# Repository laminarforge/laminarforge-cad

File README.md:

# laminarforge-cad

Parametric CAD models for the LaminarForge open-source diagnostics platform, written in Rust using the [`vcad`](https://crates.io/crates/vcad) crate. Core LAMP/CRISPR device CAD is now built around a sealed disposable diagnostic cartridge rather than loose PCR tubes. Shared constants live in `src/lib.rs`, device and validation generators live in `src/bin/`, and PCB routing lives in `src/pcb/`.

## Local iteration

Use the local `laminarforge_build` MCP tool with an explicit `bin`:

| Change | Action | Purpose |
| --- | --- | --- |
| Rust source validation | `check` | Check one target without code generation. |
| Rust source needs execution | `run`, profile `dev` | Build and run one target. |
| Runtime TOML only, executable already built from the intended source | `execute`, profile `dev` | Generate outputs without invoking Cargo. |
| Final optimized output | `run`, profile `release` | Explicitly optimize the selected target. |

The priming fixture accepts runtime TOML. Other models vary: some already read
configuration, while others use compiled constants. See [the iteration guide](docs/cad-iteration.md)
for exact tool arguments and verification requirements, and [the workflow audit](docs/cad-workflow-audit-2026-09-13.md)
for the remaining improvements.

## Source and delivery

`main` is canonical. Builds and CAD generation run locally on the Mac. AWS,
GitHub Actions and Namespace processing are retired; GitHub stores source only.
Pushing or tagging does not build or publish model outputs. Validate each
changed model and deliver its explicit output files through the local workflow.
PCB manufacturing output must also pass the [routing and release standard](docs/pcba_routing_and_release_standard.md).

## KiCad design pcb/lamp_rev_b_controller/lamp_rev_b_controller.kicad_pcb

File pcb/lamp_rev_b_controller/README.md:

# LAMP Rev B Controller PCBA

Source-package ticket: `T-4C206871`<br>
Manufacturer-handoff ticket: `T-E36FA2C2`<br>
Electrical release evidence: `A-9F7C4851`

This directory is the deterministic source for the Rev B controller carrier. The promoted copper/electrical design is fabrication-clean. Manufacturer-order readiness is a separate fail-closed state owned by `lamp_rev_b_controller_fab_release`.

## Routing and release policy

All routing and manufacturer-release work is governed by the mandatory [LaminarForge PCBA Routing and Release Standard](../../docs/pcba_routing_and_release_standard.md). The board-specific fixture and evidence are:

- [`freerouting_benchmark.toml`](freerouting_benchmark.toml): pinned router/tool settings and the 1,200-second runtime cap;
- [`freerouting_benchmark.md`](freerouting_benchmark.md): harness operation and determinism limitations;
- [`benchmarks/freerouting_v2_1_0_pass_sweep.md`](benchmarks/freerouting_v2_1_0_pass_sweep.md) and its [JSON record](benchmarks/freerouting_v2_1_0_pass_sweep.json): exact 1→10→50 matrix evidence;
- [`benchmarks/freerouting_v2_1_0_promotion.md`](benchmarks/freerouting_v2_1_0_promotion.md): first-clean promotion-attempt evidence; and
- [`electrical_release_evidence.md`](electrical_release_evidence.md), [`fab_release.toml`](fab_release.toml), and [`release_manifest.toml`](release_manifest.toml): electrical, fabrication, and deterministic-package gates.

These files specialize the general policy for Rev B; they do not replace it. Routing and SES validation remain scratch-only until every promotion gate passes.

## Locked first-article population

- Variant: `rev_b_12v_first_article`; 5 assembled top-side PCBAs.
- `R25` and `R26`: mandatory DNP. Populating either bypasses its heater MOSFET and can energize the heater whenever `VIN_HEATER` is present.
- `R55`: populate only for this 12 V variant; DNP for 24 V unless an approved regulated 12 V VDRV path is present.
- `J24`: connect through an external normally-closed thermal cutoff or a correctly rated jumper before heater tests. Do not bridge `VIN_PROTECTED` to `VIN_HEATER` in copper.
- `LDD-1000H` and `P7812-500R` alternates: DNP for this release.
- Panelization: fabricator-owned from the released single-up board; portal preview approval is mandatory.

## Authoritative workflow

Run the repository contract and release command through the LaminarForge build tool:

```json
{"repo":"laminarforge-cad","action":"run","bin":"lamp_rev_b_controller_check"}
```

```json
{"repo":"laminarforge-cad","action":"run","bin":"lamp_rev_b_controller_fab_release"}
```

The release command requires a clean full commit equal to `origin/main` and KiCad `10.0.3`. It writes every KiCad report/export to two ignored temporary trees, normalizes known time metadata, compares every staged byte, and promotes only identical results.

When every external choice is controlled, it emits:

- nine fabrication Gerbers plus the Gerber job file;
- separate F/B paste Gerbers;
- separate PTH/NPTH Excellon drills, both drill maps, and drill report;
- fabrication and top/bottom assembly PDFs;
- formal BOM, CPL, DNP, and no-substitution CSVs;
- schematic PDF, top/bottom renders, board-only mechanical STEP, source snapshot, notes, and electrical evidence;
- `MANIFEST.json`, `SHA256SUMS`, upload units, and a normalized outer handoff ZIP.

If procurement, stackup/order fields, or portal approval remain unresolved, it still preserves the byte-reproducible review tree and exact blocker report, exits nonzero, and emits neither `upload/` nor the outer handoff ZIP.

## Current external blockers

Repository evidence does not define a selected manufacturer/order profile, physical dielectric stackup, fabrication tolerances/class, final finish specification, colors, or an impedance-policy decision. `parts.toml` also lacks explicit manufacturer/MPN fields and contains unresolved supplier prose/manual selections. No portal preview has been approved. These are manufacturing choices, not electrical design defects; do not invent them and do not treat the provisional artifact `A-D87AC12B` as vendor-cited research.

Any source, population, placement, schematic, stackup, or copper change invalidates prior evidence and requires fresh DRC/connectivity/ERC/BOM/CPL/reproducibility gates.

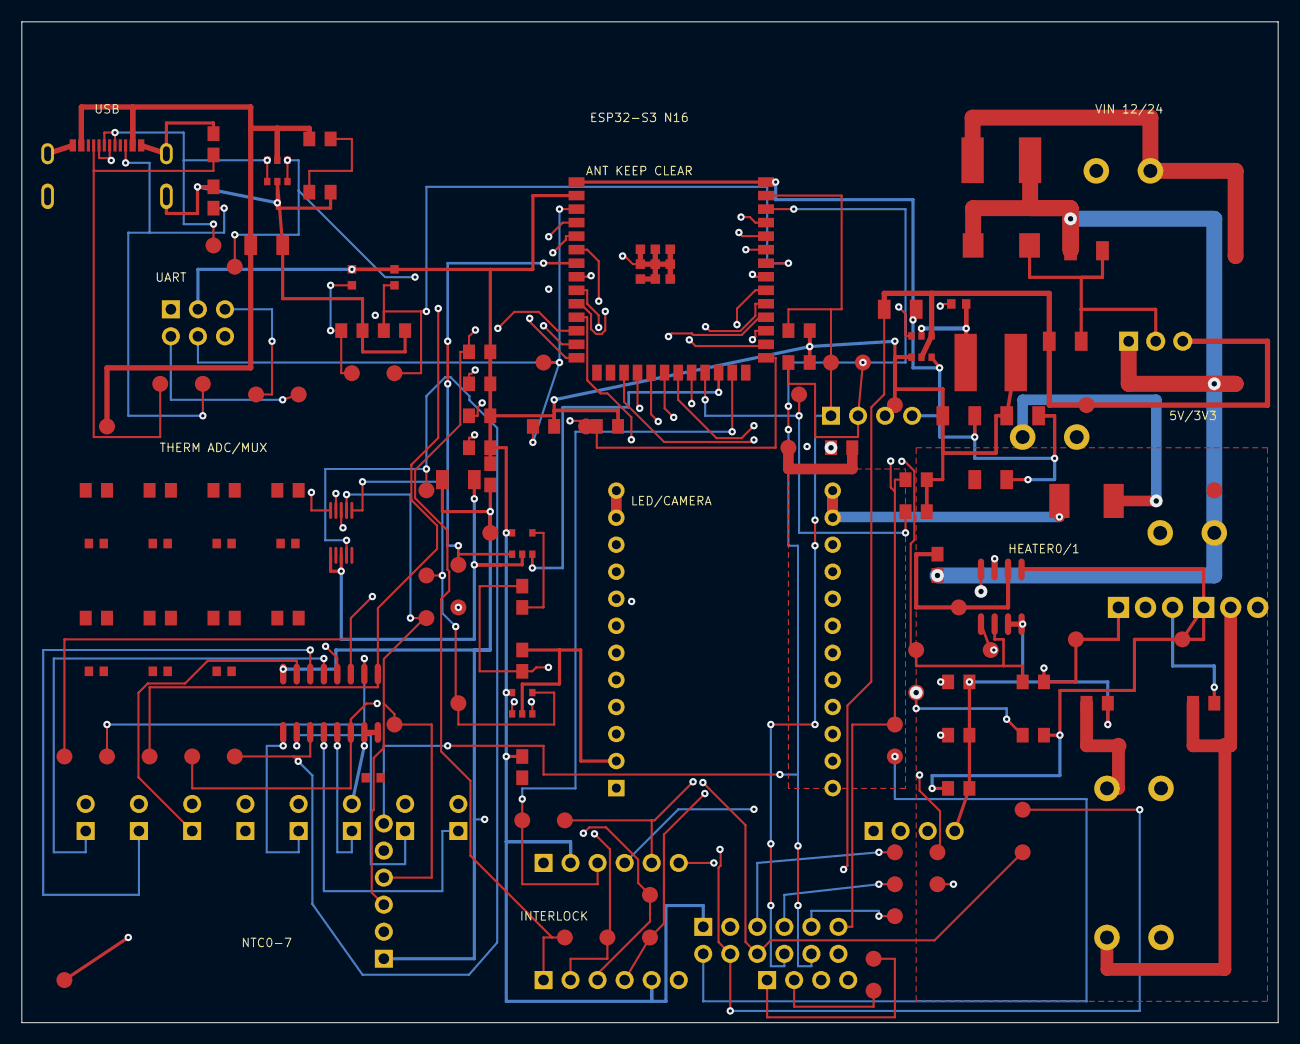
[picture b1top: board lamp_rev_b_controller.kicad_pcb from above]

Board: 4 copper layers, 118.0 x 94.0 mm, 153 parts (0 on the bottom side), 72 nets.

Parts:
C1, C5, C6: 22uF rail bulk; C1206
C2: 22uF >=10V +5V buck output; C1206
C3: 22uF AP63203 input; C1206
C4: 22uF 50V VIN buck input; C1206
C7, C8: 22uF AP63203 output; C1206
C9: 100nF bootstrap; C0603
C10, C11, C12, C13, C14, C15, C16, C17: 100nF; C0603
D1: SMBJ18A footprint option; SMB_L4.6-W3.6-LS5.3-RD
D2, D3: LED0603 status; LED0603-RD
F1: RUEF500K/PTC; FUSE2920
FB1: 0805 ferrite bead / approved analog rail link fro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; R0805
J1: TYPE-C 3.1 MT 16P; USB-C-SMD_TYPE-C-USB-4
J2, J12, J13, J15: DB128H-5.08-2P-BK-S; TERM-BLOCK-5.08-2P
J4, J5, J6, J7, J8, J9, J10, J11: 2-pin NTC header; PINHEADER_1X02_2.54MM
J16: LED NTC/ID header; PINHEADER_1X04_2.54MM
J17: External camera sync header; PINHEADER_1X06_2.54MM
J18: SPI/FIFO camera module header; PINHEADER_2X06_2.54MM
J19: Lid/cartridge/cutoff interlock header; PINHEADER_1X06_2.54MM
J20: Fan PWM/tach header; PINHEADER_1X04_2.54MM
J21: 2x3 UART/programming header; PINHEADER_2X03_2.54MM
J22: I2C expansion header; PINHEADER_1X04_2.54MM
J23: Analog optical diagnostic header; PINHEADER_1X06_2.54MM
J24: DB128H-5.08-2P high-current heater cutoff loop/li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; TERM-BLOCK-5.08-2P
L1: Wurth 74439346068 6.8uH shielded inductor; IND_74439346068
Q1, Q2: IRLB3813PBF TO-220 12V prototype; TO-220-3_VERTICAL
R1, R2: 5.1k; R0805
R3, R4: 100k/100k VBUS sense; R0805
R10, R11, R12, R13, R14, R15, R16, R17: 10k 0.1%; R0805
R20, R21: 33R; R0805
R22, R23, R24, R48, R49: 10k; R0805
R25, R26: 50mR DNP option; R0805
R30, R31: 1k; R0805
R40, R41, R42, R43, R44, R45, R46, R47: 4.7k; R0805
R50: 100R LED DIM series; R0805
R51: 100k LED DIM pulldown; R0805
R52: 0R LED_SUPPLY feed link from VIN_PROTECTED; R0805
R53: 0.1R 1% >=1W LED current shunt; R2512
R54: 10k LED_FAULT_N pull-up; R0805
R55: 0R VDRV feed link from VIN_PROTECTED, 12 V popula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; R0805
TP_3V3: +3V3; TESTPOINT_SMD_1.5MM
TP_3V3A: +3V3_ANA; TESTPOINT_SMD_1.5MM
TP_5V: +5V; TESTPOINT_SMD_1.5MM
TP_ADS_AIN0: THERM_MUX_OUT; TESTPOINT_SMD_1.5MM
TP_ADS_AIN2: LED_CURRENT_SENSE; TESTPOINT_SMD_1.5MM
TP_ADS_AIN3: AUX_ANALOG_IN; TESTPOINT_SMD_1.5MM
TP_AUX_ANALOG: AUX_ANALOG_IN; TESTPOINT_SMD_1.5MM
TP_BOOT: ESP_GPIO0_BOOT; TESTPOINT_SMD_1.5MM
TP_CAM_CS: CAM_CS_N; TESTPOINT_SMD_1.5MM
TP_CAM_FRAME: CAM_FRAME_INT; TESTPOINT_SMD_1.5MM
TP_CAM_PWDN: CAM_PWDN_N; TESTPOINT_SMD_1.5MM
TP_CAM_RESET: CAM_RESET_N; TESTPOINT_SMD_1.5MM
TP_CART: CART_PRESENT_N; TESTPOINT_SMD_1.5MM
TP_CUTOFF: AUX_IO0_THERMAL_CUTOFF_OK; TESTPOINT_SMD_1.5MM
TP_EN: ESP_EN; TESTPOINT_SMD_1.5MM
TP_EXPOSURE: EXPOSURE_ACTIVE_IN; TESTPOINT_SMD_1.5MM
TP_FAN_PWM: FAN_PWM; TESTPOINT_SMD_1.5MM
TP_FAN_TACH: FAN_TACH; TESTPOINT_SMD_1.5MM
TP_FAULT: STATUS_FAULT_LED; TESTPOINT_SMD_1.5MM
TP_FRAME_TRIG: FRAME_TRIG_OUT; TESTPOINT_SMD_1.5MM
TP_GND: GND; TESTPOINT_SMD_1.5MM
TP_HEATER0_GATE: HEATER0_GATE; TESTPOINT_SMD_1.5MM
TP_HEATER0_LOW: HEATER0_LOW; TESTPOINT_SMD_1.5MM
TP_HEATER0_PWM: HEATER0_PWM; TESTPOINT_SMD_1.5MM
TP_HEATER1_GATE: HEATER1_GATE; TESTPOINT_SMD_1.5MM
TP_HEATER1_LOW: HEATER1_LOW; TESTPOINT_SMD_1.5MM
TP_HEATER1_PWM: HEATER1_PWM; TESTPOINT_SMD_1.5MM
TP_HEATER_ARM: HEATER_ARM; TESTPOINT_SMD_1.5MM
TP_I2C_SCL: I2C_SCL; TESTPOINT_SMD_1.5MM
TP_I2C_SDA: I2C_SDA; TESTPOINT_SMD_1.5MM
TP_LATCH: LATCH_LOCKED_N; TESTPOINT_SMD_1.5MM
TP_LED_EN: LED_EXC_EN; TESTPOINT_SMD_1.5MM
TP_LED_PWM: LED_EXC_PWM; TESTPOINT_SMD_1.5MM
TP_LED_SENSE: LED_CURRENT_SENSE; TESTPOINT_SMD_1.5MM
TP_LED_SUPPLY: LED_SUPPLY; TESTPOINT_SMD_1.5MM
TP_LED_SYNC: LED_SYNC_OUT; TESTPOINT_SMD_1.5MM
TP_LID: LID_CLOSED_N; TESTPOINT_SMD_1.5MM
TP_RUN: STATUS_RUN_LED; TESTPOINT_SMD_1.5MM
TP_SD_CS: SD_CS_N; TESTPOINT_SMD_1.5MM
TP_SPARE42: SPARE_GPIO42; TESTPOINT_SMD_1.5MM
TP_SPI_MISO: SPI_MISO; TESTPOINT_SMD_1.5MM
TP_SPI_MOSI: SPI_MOSI; TESTPOINT_SMD_1.5MM
TP_SPI_SCLK: SPI_SCLK; TESTPOINT_SMD_1.5MM
TP_THERM_EN: THERM_MUX_EN_N; TESTPOINT_SMD_1.5MM
TP_THERM_OUT: THERM_MUX_OUT; TESTPOINT_SMD_1.5MM
TP_THERM_S0: THERM_MUX_S0; TESTPOINT_SMD_1.5MM
TP_THERM_S1: THERM_MUX_S1; TESTPOINT_SMD_1.5MM
TP_THERM_S2: THERM_MUX_S2; TESTPOINT_SMD_1.5MM
TP_UART_RX: UART0_RXD; TESTPOINT_SMD_1.5MM
TP_UART_TX: UART0_TXD; TESTPOINT_SMD_1.5MM
TP_USB_CC1: USB_CC1; TESTPOINT_SMD_1.5MM
TP_USB_CC2: USB_CC2; TESTPOINT_SMD_1.5MM
TP_USB_DN: USB_DN; TESTPOINT_SMD_1.5MM
TP_USB_DP: USB_DP; TESTPOINT_SMD_1.5MM
TP_VBUS: VBUS; TESTPOINT_SMD_1.5MM
TP_VDRV: VDRV; TESTPOINT_SMD_1.5MM
TP_VIN: VIN_12_24; TESTPOINT_SMD_1.5MM
TP_VIN_HEATER: VIN_HEATER; TESTPOINT_SMD_1.5MM
TP_VIN_PROT: VIN_PROTECTED; TESTPOINT_SMD_1.5MM
U1: ESP32-S3-WROOM-1-N16; WIFIM-SMD_ESP32-S3-WROOM-1-N8
U2: USBLC6-2SC6; SOT-23-6
U3: Diodes AP63203WU-7 fixed 3.3V 2A buck; TSOT26_AP63203WU
U4: ADS1115IDGSR; MSOP-10_L3.0-W3.0-P0.50-LS5.0-BL
U5: CD74HC4051M; SOIC-16_L9.9-W3.9-P1.27-LS6.0-BL
U6: TC4427ACOA/TC4427EPA; SOIC-8_L4.9-W3.9-P1.27-LS6.0-BL
U7: CUI/Bel P7805-2000-S 5V 2A 8-36V buck module; han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; P78-2000-S_SIP3
U8: Mean Well LDD-700H 700mA CC buck LED driver; LDD-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; MEANWELL_LDD-300-1000H_THT
U9: SN74LVC1G08DBVR LED_EXC_PWM AND LED_EXC_EN; SOT-23-5
U10: INA180A1IDBVR gain 20 LED current sense; SOT-23-5

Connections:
3V3_BST: C9.1, U3.6
3V3_SW: C9.2, L1.1, U3.5
+3V3: C7.1, C8.1, D2.2, D3.2, FB1.1, J17.2, J18.1, J19.5, J21.2, J22.3, L1.2, R40.2, R41.2, R42.2, R43.2, R44.2, R45.2, R46.2, R47.2, R48.2, R49.2, R54.2, TP_3V3.1, U1.2, U3.1, U4.8, U9.5, U10.5
+3V3_ANA: C5.1, FB1.2, J16.3, J23.1, TP_3V3A.1, U5.16
+5V: C2.1, C3.1, J20.3, TP_5V.1, U3.2, U3.4, U7.3
AUX_ANALOG_IN: J16.2, J23.3, J23.4, TP_ADS_AIN3.1, TP_AUX_ANALOG.1, U4.7
AUX_IO0_THERMAL_CUTOFF_OK: J19.4, R47.1, TP_CUTOFF.1, U1.32
CAM_CS_N: J18.6, R42.1, TP_CAM_CS.1, U1.20
CAM_FRAME_INT: J18.7, TP_CAM_FRAME.1, U1.21
CAM_PWDN_N: J18.9, TP_CAM_PWDN.1, U1.22
CAM_RESET_N: J18.8, TP_CAM_RESET.1, U1.8
CART_PRESENT_N: J19.2, R45.1, TP_CART.1, U1.31
ESP_EN: J21.5, R48.1, TP_EN.1, U1.3
ESP_GPIO0_BOOT: J21.6, R49.1, TP_BOOT.1, U1.27
EXPOSURE_ACTIVE_IN: J17.4, TP_EXPOSURE.1, U1.29
FAN_PWM: J20.1, TP_FAN_PWM.1
FAN_TACH: J20.2, TP_FAN_TACH.1
FRAME_TRIG_OUT: J17.3, TP_FRAME_TRIG.1, U1.25
GND: C1.2, C2.2, C3.2, C4.2, C5.2, C6.2, C7.2, C8.2, D1.2, J1.13, J1.14, J1.15, J1.16, J1.A12B1, J1.B12A1, J2.2, J4.2, J5.2, J6.2, J7.2, J8.2, J9.2, J10.2, J11.2, J16.4, J17.1, J18.2, J18.12, J19.6, J20.4, J21.1, J22.4, J23.2, Q1.3, Q2.3, R1.2, R2.2, R4.2, R22.2, R23.2, R24.2, R25.2, R26.2, R30.2, R31.2, R51.2, TP_GND.1, U1.1, U1.40, U1.41, U2.2, U3.3, U4.1, U4.3, U5.7, U5.8, U6.3, U6.4, U7.2, U8.1, U8.2, U9.2, U10.2
HEATER0_GATE: Q1.1, R20.2, R23.1, TP_HEATER0_GATE.1, U6.7
HEATER0_LOW: J12.2, Q1.2, R25.1, TP_HEATER0_LOW.1
HEATER0_PWM: R20.1, TP_HEATER0_PWM.1, U1.10, U6.2
HEATER1_GATE: Q2.1, R21.2, R24.1, TP_HEATER1_GATE.1, U6.5
HEATER1_LOW: J13.2, Q2.2, R26.1, TP_HEATER1_LOW.1
HEATER1_PWM: R21.1, TP_HEATER1_PWM.1, U1.11, U6.8
HEATER_ARM: R22.1, TP_HEATER_ARM.1, U1.9, U6.1
I2C_SCL: J18.11, J22.2, J23.6, R41.1, TP_I2C_SCL.1, U1.38, U4.10
I2C_SDA: J18.10, J22.1, J23.5, R40.1, TP_I2C_SDA.1, U1.39, U4.9
LATCH_LOCKED_N: J19.3, R46.1, TP_LATCH.1
LED_CURRENT_SENSE: TP_ADS_AIN2.1, TP_LED_SENSE.1, U4.6, U10.4
LED_DIM_DRIVE: R50.2, R51.1, U8.22
LED_DIM_GATE: R50.1, U9.4
LED_DRV_PLUS: R53.1, U8.13, U8.14, U10.1
LED_EXC_EN: TP_LED_EN.1, U1.24, U9.3
LED_EXC_PWM: TP_LED_PWM.1, U1.7, U9.1
LED_MINUS: J15.2, U8.11, U8.12
LED_PLUS: J15.1, R53.2, U10.3
LED_SUPPLY: R52.2, TP_LED_SUPPLY.1, U8.23, U8.24
LED_SYNC_OUT: J17.5, TP_LED_SYNC.1, U1.28
LID_CLOSED_N: J19.1, R44.1, TP_LID.1, U1.30
SD_CS_N: R43.1, TP_SD_CS.1, U1.23
SPARE_GPIO42: J17.6, TP_SPARE42.1, U1.35
SPI_MISO: J18.5, TP_SPI_MISO.1, U1.19
SPI_MOSI: J18.4, TP_SPI_MOSI.1, U1.18
SPI_SCLK: J18.3, TP_SPI_SCLK.1, U1.17
STATUS_FAULT_LED: D3.1, R31.1, TP_FAULT.1, U1.34
STATUS_RUN_LED: D2.1, R30.1, TP_RUN.1, U1.33
THERM_CH_0: J4.1, U5.13
THERM_CH_1: J5.1, U5.14
THERM_CH_2: J6.1, U5.15
THERM_CH_3: J7.1, U5.12
THERM_CH_4: J8.1, U5.1
THERM_CH_5: J9.1, J16.1, U5.5
THERM_CH_6: J10.1, U5.2
THERM_CH_7: J11.1, U5.4
THERM_MUX_EN_N: TP_THERM_EN.1, U1.12, U5.6
THERM_MUX_OUT: TP_ADS_AIN0.1, TP_THERM_OUT.1, U4.4, U5.3
THERM_MUX_S0: TP_THERM_S0.1, U1.4, U5.11
THERM_MUX_S1: TP_THERM_S1.1, U1.5, U5.10
THERM_MUX_S2: TP_THERM_S2.1, U1.6, U5.9
UART0_RXD: J21.4, TP_UART_RX.1, U1.36
UART0_TXD: J21.3, TP_UART_TX.1, U1.37
USB_CC1: J1.A5, R1.1, TP_USB_CC1.1
USB_CC2: J1.B5, R2.1, TP_USB_CC2.1
USB_DN: J1.A7, J1.B7, TP_USB_DN.1, U1.13, U2.3, U2.4
USB_DP: J1.A6, J1.B6, TP_USB_DP.1, U1.14, U2.1, U2.6
USB_VBUS_SENSE: R3.2, R4.1
VBUS: C1.1, J1.A9B4, J1.B9A4, R3.1, TP_VBUS.1, U2.5
VDRV: R55.2, TP_VDRV.1, U6.6
VIN_12_24: F1.1, J2.1, TP_VIN.1
VIN_HEATER: C6.1, J12.1, J13.1, J24.2, TP_VIN_HEATER.1
VIN_PROTECTED: C4.1, D1.1, F1.2, J24.1, R52.1, R55.1, TP_VIN_PROT.1, U7.1

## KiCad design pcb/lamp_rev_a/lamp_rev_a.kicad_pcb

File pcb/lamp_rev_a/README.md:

# LaminarForge LAMP Rev A PCBA

This directory is the source package for the real one-board LAMP PCBA.

The goal is one 4-layer ESP32-S3 board that can be checked, laid out in KiCad,
exported for JLCPCB, and iterated without going back to the old generated-layout
workflow.

## Source Of Truth

- `contract.toml`: board requirements, rails, nets, GPIO map, test points, and verification gates.
- `parts.toml`: selected schematic parts plus explicit fab-blocking part-selection gaps.
- `power_architecture.toml`: locked Rev A power topology and the explicit no-buck decision.
- `optical_architecture.toml`: locked Rev A optical topology, wavelength, detector, and front-end decision.
- `optical_mode.md`: human-readable optical-mode decision and bench validation gate.
- `placement.toml`: locked starting refs, coordinates, test points, and eight-slot optical geometry.
- `pin_nets.toml`: conservative footprint pad-to-net assignments for known package pinouts.
- `firmware_handoff.toml`: ESP32-S3 module-pin to SoC-GPIO handoff, slot map, and firmware bring-up notes.
- `electrical_validation.toml`: pre-fab electrical validation assumptions, derating gates, current-path checks, and simulation handoff sources.
- `routing_plan.toml`: routing phase order, current unrouted count, autorouter policy, and release gates.
- `routing_seed.toml`: DRC-clean starter traces emitted into the materialized board.
- `copper_zones.toml`: controlled KiCad copper pours, starting with front/back GND zones.
- `fab_release.toml`: repeatable KiCad CLI export contract for Gerbers, drill files, assembly files, STEP, and release reports.
- `lamp_rev_a.kicad_sch`: KiCad schematic shell for the one-board Rev A electrical architecture.
- `lamp_rev_a.kicad_pcb`: materialized KiCad board with the Rev A outline, 4-layer stack, placed footprints, test points, and optical-slot guides.
- `lamp_rev_a.kicad_pro`: KiCad project shell.
- `sym-lib-table` / `fp-lib-table`: project-local library tables pointing at the locked `pcb/lib/lcsc` symbols and footprints.
- `lamp_rev_a.kicad_dru`: custom KiCad design rules for power, heater, analog, and USB constraints.
- `kibot.yaml`: intended fab/report export pipeline once the schematic and placed board exist.

Rust should validate contracts and automate exports. KiCad should own the
schematic and PCB layout.

## Iteration Flow

```text
contract.toml + parts.toml
  -> cargo run --release --bin lamp_pcba_check
  -> placement.toml refs and zone checks
  -> pin_nets.toml trusted pad assignments
  -> firmware_handoff.toml firmware pin/slot handoff checks
  -> electrical_validation.toml power, derating, heater, GPIO, USB, and simulation checks
  -> cargo run --release --bin lamp_rev_a_materialize_board
  -> cargo run --release --bin lamp_rev_a_seed_routes_from_drc when reseeding short safe traces
  -> cargo run --release --bin lamp_rev_a_route_greedy for DRC-gated route iteration
  -> kicad-cli pcb drc --refill-zones for zone-connected routing checks
  -> KiCad schematic capture in lamp_rev_a.kicad_sch
  -> KiCad ERC
  -> footprint/BOM/JLC field lock
  -> KiCad placement cleanup from the materialized board
  -> KiCad interactive routing
  -> KiCad DRC + schematic/PCB parity
  -> KiBot/KiKit fab outputs
  -> physical bring-up measurements
  -> update contract.toml for the next revision
```

## Board Decisions

- One physical board for Rev A.
- 4-layer stack: `F.Cu`, `In1.Cu` ground plane, `In2.Cu` power plane, `B.Cu`.
- ESP32-S3 module, not a bare ESP32 chip.
- USB VBUS is the Rev A electronics 5 V source through a Schottky path; +3V3 is derived locally.
- The 12 V input is reserved for heater power. Do not add a 12 V to 5 V buck unless standalone non-USB operation becomes a new explicit Rev change.
- External heater element driven from the board through a protected high-current output.
- Heater path protection is locked as board-side resettable fuse + TVS + 5.08 mm heater terminal, with an external inline KSD9700 thermal cutoff mounted on the heater assembly.
- Optical mode is locked to 650 nm red-light turbidimetry with eight LED/photodiode channels, muxed into one TIA and ADC path.
- Starting placement is locked in `placement.toml`: 91 top-side footprints, 16 test points, and 8 optical slots at 12 mm pitch.
- Test points are mandatory for rails, heater control/output, I2C, UART, boot/reset, ADC, and mux output.

## Local Checks

Run:

```bash
cargo run --release --bin lamp_pcba_check
cargo run --release --bin lamp_rev_a_electrical_validate
cargo run --release --bin lamp_rev_a_spice_check
cargo run --release --bin lamp_rev_a_materialize_board
cargo run --release --bin lamp_rev_a_fab_preview
cargo run --release --bin lamp_rev_a_fab_release
cargo run --release --bin lamp_rev_a_route_report
cargo build --release --bin lamp_rev_a_materialize_board --bin lamp_rev_a_route_greedy
LAMP_ROUTE_MAX_ACCEPTS=10 LAMP_ROUTE_MAX_TRIALS=160 target/release/lamp_rev_a_route_greedy
```

`lamp_rev_a_spice_check` requires `ngspice`. `main` CI installs it, runs the
operating-point check against the generated power-path netlist, then runs
`lamp_rev_a_fab_release` on a KiCad-enabled macOS runner and uploads
`lamp-rev-a-pcba-fab-release-<commit>` containing the validated fab release
directory and upload bundles.

The current schematic is an architecture shell, not a fabrication-ready circuit.
The checker should not report fab-blocking part-selection gaps. The board now
materializes all selected parts into KiCad with zero physical DRC violations
with a DRC-clean starter route seed and GND copper pours. The route seed is
currently at 112 accepted segments, zero real unrouted ratlines after KiCad zone
refill, and one ignored KiCad self-zone report item for the front GND pour. The
active work is schematic completion, schematic/PCB parity, fab export validation,
and bench validation.
`lamp_rev_a_fab_release` emits JLCPCB machine-assembly BOM/CPL files separately
from through-hole/manual-install parts, then verifies that required Gerbers,
drills, reports, position files, review STEP output, and the order audit report
are present and non-empty. It also emits validated upload bundles under
`fab_release/bundles/`: fabrication Gerbers/drills, assembly CSVs, and review
artifacts. The release also includes a source snapshot bundle with the exact
KiCad and TOML inputs used to generate the fab package. The review package
includes a bring-up checklist generated from the configured Rev A test points
and a firmware handoff generated from the checked ESP32-S3 pin map. It also
emits an electrical-validation report, a first-order SPICE power-path handoff,
a machine-checked full-speed USB DP/DN routing sanity gate, a
simulation/analysis handoff, generated PDN current-path and thermal power CSVs,
a structured first-article measurement CSV for current-limited rail bring-up,
component derating/stress CSVs for the high-risk electrical parts,
an EMC/ESD pre-compliance CSV for USB, heater, 12 V, Wi-Fi, and analog noise risks,
a USB-C power-budget CSV for Rd/default-current, VBUS/+5V/+3V3 current, inrush linkage, and first-article rail coverage,
a procurement-readiness CSV for critical part ordering, machine/manual assembly, and external safety-component evidence,
a procurement-substitution CSV locking safety-critical LCSC order codes and requiring engineering review for swaps,
a schematic source/parity CSV tying the architecture-shell KiCad schematic to contract modules, selected parts, and required nets,
a connector/polarity CSV for USB-C, manual connectors, diodes, MOSFETs, and orientation-sensitive IC pinouts,
an assembly-orientation CSV for machine-placed ICs, polarity-sensitive parts, CPL centroids, and pin-1 evidence,
an assembly-inspection CSV requiring AOI/photo evidence, linked validation gates, and stop/rework actions for critical parts,
an assembly-fixture/readability CSV requiring visible silkscreen labels, fixture references, photo evidence, and rework actions for critical connectors/test points,
a machine-checked assembly-parity CSV for BOM/CPL/manual/position reference consistency,
a fabrication-capability CSV for board-house stackup, geometry, drill, via, and routing process limits,
an I2C/ADS1115 bus validation CSV for pull-up, rise-time, device identity, and stuck-low coverage,
a heater-protection coordination CSV for PTC, terminal, MOSFET, TVS, external cutoff, and current-limit coverage,
an external-harness safety CSV for 12 V adapter, heater leads, inline cutoff, wire gauge, polarity, and strain relief,
a mechanical-access CSV for service connector, heater terminal, MOSFET, boot/reset, analog, and I2C probe reachability,
an ESP32-S3 startup-safety CSV for boot straps, reset, and heater fail-closed defaults,
a manufacturing-test coverage CSV for critical test points, firmware diagnostics, and release traceability,
a calibration-readiness CSV for heater, ADC, optical, sensor-bus, negative-control, and firmware identity records,
a validation-traceability CSV tying each gate to artifacts, manifest evidence, CI steps, and pass criteria,
a simulation-input CSV for PDN, electrothermal, USB/SI, and EMC handoff readiness,
the first routed-geometry DC PDN simulation CSV for voltage drop and I2R loss,
a lumped thermal-margin simulation CSV for component and routed-copper steady-state estimates,
a heater/reaction-block thermal transient CSV for warm-up, hold, duty, overshoot, and energy estimates,
an ngspice ESP32-S3 reset/boot-strap timing netlist/CSV for EN, GPIO0, and boot-sensitive output startup checks,
an ngspice USB/VBUS hot-plug and 3.3 V startup/inrush netlist/CSV for rail startup envelope checks,
an ngspice 3.3 V rail load-step transient netlist/CSV for ESP32 burst-load sag,
an ngspice power-domain fault/backfeed netlist/CSV for 12 V heater-domain isolation assumptions,
an ngspice optical analog front-end transient netlist/CSV for TIA/ADC signal-envelope range,
an optical crosstalk/mux-settling CSV for slot isolation and ADC sampling assumptions,
an optical signal/noise margin CSV for threshold and negative-control drift assumptions,
and a thermistor/ADC transfer CSV for heater temperature-sense range, sensitivity, and fault coverage,
and a checksum manifest for the fabrication, assembly, and source bundles.
It also mirrors the board STEP review model to `output/lamp_rev_a_board.stp`;
run the CAD conversion for `lamp_rev_a_board` to create
`output/lamp_rev_a_board.usdz` for the Agentic FlowState CAD tab.

Current KiCad checks:

```bash
kicad-cli sch erc pcb/lamp_rev_a/lamp_rev_a.kicad_sch \
  -o pcb/lamp_rev_a/reports/erc.json --format json

kicad-cli pcb drc --refill-zones --format json \
  --output pcb/lamp_rev_a/reports/drc.json \
  pcb/lamp_rev_a/lamp_rev_a.kicad_pcb
```

Expected DRC state at this stage: `0 violations` and no real unrouted
connections. KiCad may still report one self-referential front-GND-zone
`unconnected_items` entry; `lamp_rev_a_route_report` ignores only that exact
self-zone artifact and still reports real ratlines by net.

`lamp_rev_a_seed_routes_from_drc` is intentionally conservative: it only seeds
short direct routes that preserve zero physical DRC violations. Longer routes
must be added deliberately in `routing_seed.toml`, accepted by
`lamp_rev_a_route_greedy`, or finished in KiCad. `lamp_rev_a_route_greedy`
mechanically tries candidate routes, runs KiCad DRC, and keeps only candidates
that reduce `unconnected_items` while preserving zero physical DRC violations.

Do not accept autorouter output by itself. Use it to expose bad placement or
constraint problems, then finish and review the layout in KiCad.

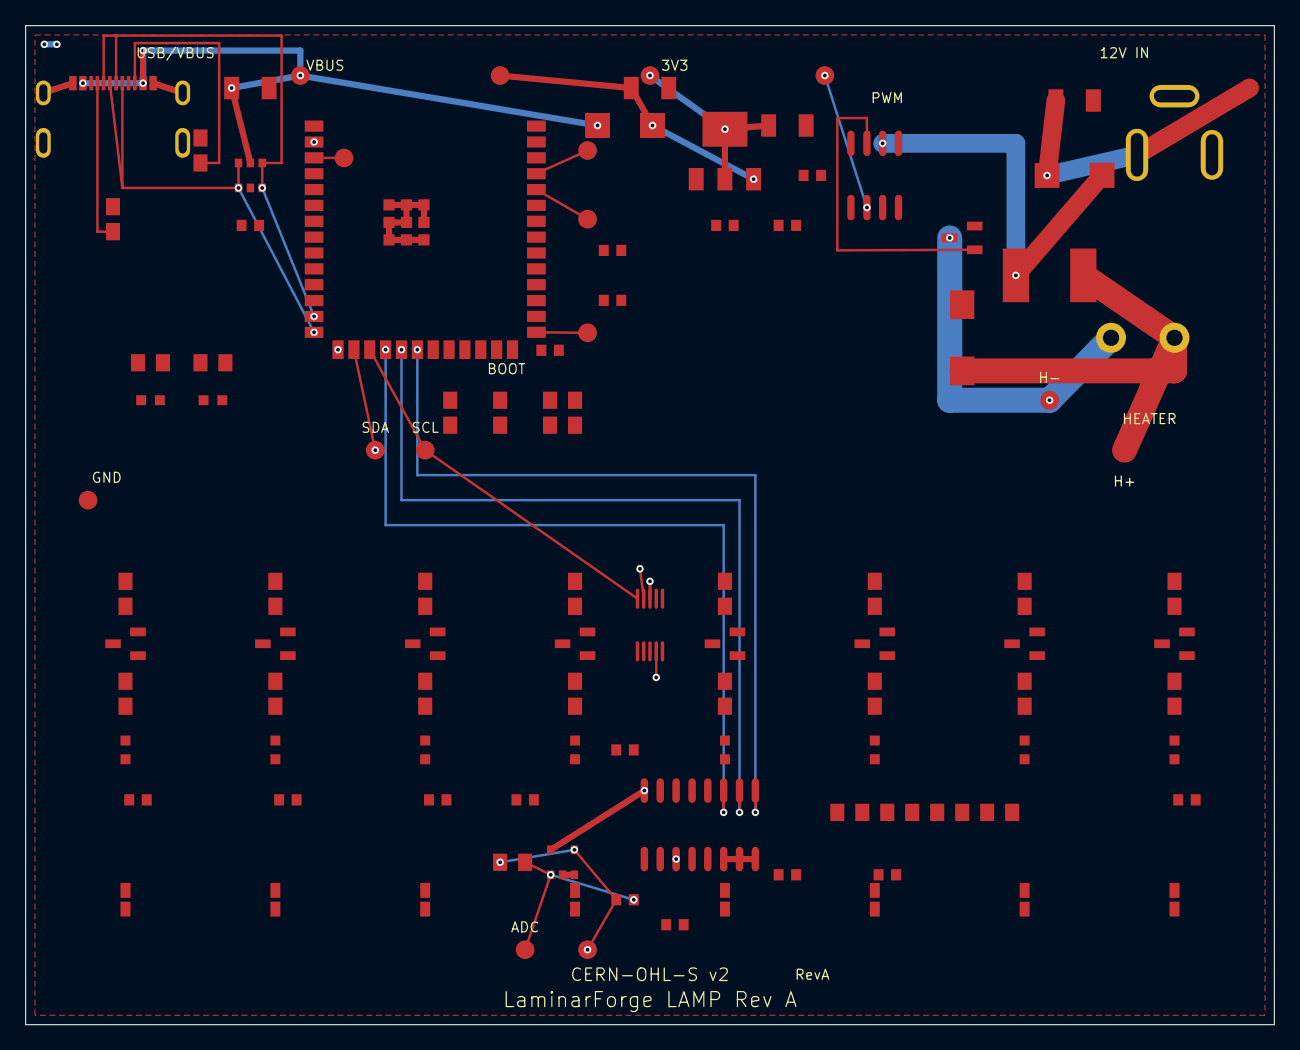
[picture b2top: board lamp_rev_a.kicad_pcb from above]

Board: 4 copper layers, 100.0 x 80.0 mm, 107 parts (0 on the bottom side), 25 nets.

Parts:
C1, C2, C3, C4: 22uF; C1206
C5: 10pF; C0603
C6, C7, C8, C9, C10, C11, C12, C13, C14, C15, C16, C17, C18, C19, C20, C21: 100nF; C0603
D1, D13: SS34; SMA_L4.3-W2.6-LS5.2-RD
D2, D3, D4, D5, D6, D7, D8, D9, D11, D12: KT-0603R; LED0603-RD
D10: SMBJ18A; SMB_L4.6-W3.6-LS5.3-RD
F1: SMD2920-300C-36V; FUSE2920
J1: TYPE-C 3.1 MT 16P; USB-C-SMD_TYPE-C-USB-4
J2: DC-005-5A-2.0; DC-IN-TH_DC-005-5A-2.0
J3: DB128H-5.08-2P-BK-S; TERM-BLOCK-5.08-2P
PD1, PD2, PD3, PD4, PD5, PD6, PD7, PD8: SFH2704; PHOTODIODE-SMD-2X1.8
Q1: AO3400A; SOT-23-3_L2.9-W1.3-P1.90-LS2.4-BR
Q2, Q3, Q4, Q5, Q6, Q7, Q8, Q9: MMBT3904; SOT-23-3_L2.9-W1.3-P1.90-LS2.4-BR
R1, R2: 5.1k; R0805
R3: 1M; R0805
R4, R5, R6, R7, R8, R9, R10, R11: 100R; R0805
R12, R13, R14, R15, R16, R17, R18, R19, R20, R21: 1k; R0805
R22, R23: 4.7k; R0805
R24, R25, R26, R27, R28, R29: 10k; R0805
TP_3V3: +3V3; TESTPOINT_SMD_1.5MM
TP_5V: +5V; TESTPOINT_SMD_1.5MM
TP_12V: +12V_RAW; TESTPOINT_SMD_1.5MM
TP_ADC: ADC_AIN1; TESTPOINT_SMD_1.5MM
TP_BOOT: ESP_GPIO0; TESTPOINT_SMD_1.5MM
TP_EN: ESP_EN; TESTPOINT_SMD_1.5MM
TP_GND: GND; TESTPOINT_SMD_1.5MM
TP_HEATER: HEATER_P; TESTPOINT_SMD_1.5MM
TP_HEATER_SUPPLY: HEATER_SUPPLY; TESTPOINT_SMD_1.5MM
TP_MUX: MUX_COM; TESTPOINT_SMD_1.5MM
TP_PWM: HEATER_PWM; TESTPOINT_SMD_1.5MM
TP_RX: UART_RX; TESTPOINT_SMD_1.5MM
TP_SCL: SCL; TESTPOINT_SMD_1.5MM
TP_SDA: SDA; TESTPOINT_SMD_1.5MM
TP_TX: UART_TX; TESTPOINT_SMD_1.5MM
TP_VBUS: VBUS; TESTPOINT_SMD_1.5MM
U1: ESP32-S3-WROOM-1-N8; WIFIM-SMD_ESP32-S3-WROOM-1-N8
U2: USBLC6-2SC6; SOT-23-6
U3: AMS1117-3.3; SOT-223
U4: ADS1115IDGSR; MSOP-10_L3.0-W3.0-P0.50-LS5.0-BL
U5: CD74HC4051M; SOIC-16_L9.9-W3.9-P1.27-LS6.0-BL
U6: TLV6001IDBVR; SOT-23-5
U7: TC4427ACOA; SOIC-8_L4.9-W3.9-P1.27-LS6.0-BL

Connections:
+3V3: C3.1, TP_3V3.1, U1.2, U3.2, U3.4, U4.8, U5.16, U6.5
+5V: C2.1, D1.2, TP_5V.1, U3.3
+12V: D13.2, F1.1, U7.6
+12V_RAW: C4.1, D13.1, J2.1, TP_12V.1
ADC_AIN1: C5.2, R3.2, TP_ADC.1, U4.4, U6.1
ESP_EN: TP_EN.1, U1.3
ESP_GPIO0: TP_BOOT.1, U1.27
GATE_DRV: Q1.1, U7.7
GND: C1.2, C2.2, C3.2, C4.2, D10.2, J1.13, J1.14, J1.15, J1.16, J1.A12B1, J1.B12A1, J2.2, J2.3, Q1.2, R1.2, R2.2, TP_GND.1, U1.1, U1.41, U2.2, U3.1, U4.1, U4.3, U5.6, U5.7, U5.8, U6.2, U6.3, U7.3
HEATER_P: J3.2, Q1.3, TP_HEATER.1
HEATER_PWM: TP_PWM.1, U1.15, U7.2
HEATER_SUPPLY: D10.1, F1.2, J3.1, TP_HEATER_SUPPLY.1
MUX_COM: C5.1, R3.1, TP_MUX.1, U5.3, U6.4
MUX_S0: U1.18, U5.11
MUX_S1: U1.19, U5.10
MUX_S2: U1.20, U5.9
SCL: TP_SCL.1, U1.17, U4.10
SDA: TP_SDA.1, U1.16, U4.9
UART_RX: TP_RX.1, U1.36
UART_TX: TP_TX.1, U1.37
USB_CC1: J1.A5, R1.1
USB_CC2: J1.B5, R2.1
USB_DN: J1.A7, J1.B7, U1.13, U2.3, U2.4
USB_DP: J1.A6, J1.B6, U1.14, U2.1, U2.6
VBUS: C1.1, D1.1, J1.A9B4, J1.B9A4, TP_VBUS.1, U2.5

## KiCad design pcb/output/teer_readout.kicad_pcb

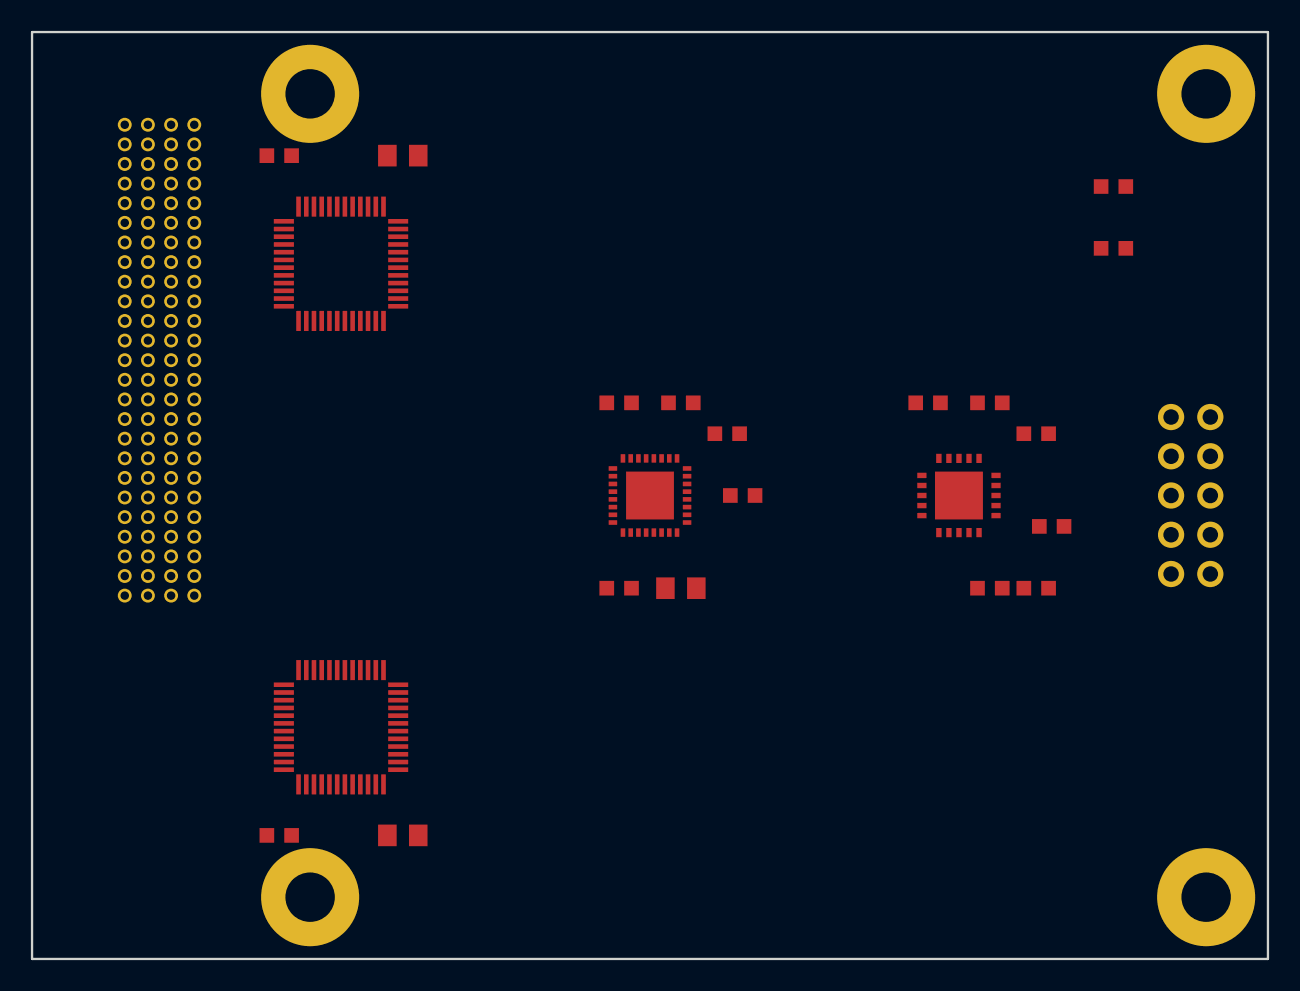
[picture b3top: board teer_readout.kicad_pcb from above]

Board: 2 copper layers, 80.0 x 60.0 mm, 127 parts (0 on the bottom side), 86 nets, no tracks yet.

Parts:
C1, C2, C3, C6, C8, C10, C11, C13: 100nF; C_0603
C4, C7, C9: 10uF; C_0805
C5: 1uF; C_0603
C12: 10nF; C_0603
FB1, FB2: BLM18PG471SN1D; R_0603
H1, H2, H3, H4: MountingHole_3.2mm_M3
J1: Header_2x5_0.1in; PinHeader_2x5_2.54mm
PP1_0: POGO_C1_CH0_IP; PogoPin_MillMax_0906
PP1_1: POGO_C1_CH0_IN; PogoPin_MillMax_0906
PP1_2: POGO_C1_CH0_VP; PogoPin_MillMax_0906
PP1_3: POGO_C1_CH0_VN; PogoPin_MillMax_0906
PP1_4: POGO_C1_CH1_IP; PogoPin_MillMax_0906
PP1_5: POGO_C1_CH1_IN; PogoPin_MillMax_0906
PP1_6: POGO_C1_CH1_VP; PogoPin_MillMax_0906
PP1_7: POGO_C1_CH1_VN; PogoPin_MillMax_0906
PP1_8: POGO_C1_CH2_IP; PogoPin_MillMax_0906
PP1_9: POGO_C1_CH2_IN; PogoPin_MillMax_0906
PP1_10: POGO_C1_CH2_VP; PogoPin_MillMax_0906
PP1_11: POGO_C1_CH2_VN; PogoPin_MillMax_0906
PP1_12: POGO_C1_CH3_IP; PogoPin_MillMax_0906
PP1_13: POGO_C1_CH3_IN; PogoPin_MillMax_0906
PP1_14: POGO_C1_CH3_VP; PogoPin_MillMax_0906
PP1_15: POGO_C1_CH3_VN; PogoPin_MillMax_0906
PP1_16: POGO_C1_RTD_FP; PogoPin_MillMax_0906
PP1_17: POGO_C1_RTD_FN; PogoPin_MillMax_0906
PP1_18: POGO_C1_RTD_SP; PogoPin_MillMax_0906
PP1_19: POGO_C1_RTD_SN; PogoPin_MillMax_0906
PP2_0: POGO_C2_CH0_IP; PogoPin_MillMax_0906
PP2_1: POGO_C2_CH0_IN; PogoPin_MillMax_0906
PP2_2: POGO_C2_CH0_VP; PogoPin_MillMax_0906
PP2_3: POGO_C2_CH0_VN; PogoPin_MillMax_0906
PP2_4: POGO_C2_CH1_IP; PogoPin_MillMax_0906
PP2_5: POGO_C2_CH1_IN; PogoPin_MillMax_0906
PP2_6: POGO_C2_CH1_VP; PogoPin_MillMax_0906
PP2_7: POGO_C2_CH1_VN; PogoPin_MillMax_0906
PP2_8: POGO_C2_CH2_IP; PogoPin_MillMax_0906
PP2_9: POGO_C2_CH2_IN; PogoPin_MillMax_0906
PP2_10: POGO_C2_CH2_VP; PogoPin_MillMax_0906
PP2_11: POGO_C2_CH2_VN; PogoPin_MillMax_0906
PP2_12: POGO_C2_CH3_IP; PogoPin_MillMax_0906
PP2_13: POGO_C2_CH3_IN; PogoPin_MillMax_0906
PP2_14: POGO_C2_CH3_VP; PogoPin_MillMax_0906
PP2_15: POGO_C2_CH3_VN; PogoPin_MillMax_0906
PP2_16: POGO_C2_RTD_FP; PogoPin_MillMax_0906
PP2_17: POGO_C2_RTD_FN; PogoPin_MillMax_0906
PP2_18: POGO_C2_RTD_SP; PogoPin_MillMax_0906
PP2_19: POGO_C2_RTD_SN; PogoPin_MillMax_0906
PP3_0: POGO_C3_CH0_IP; PogoPin_MillMax_0906
PP3_1: POGO_C3_CH0_IN; PogoPin_MillMax_0906
PP3_2: POGO_C3_CH0_VP; PogoPin_MillMax_0906
PP3_3: POGO_C3_CH0_VN; PogoPin_MillMax_0906
PP3_4: POGO_C3_CH1_IP; PogoPin_MillMax_0906
PP3_5: POGO_C3_CH1_IN; PogoPin_MillMax_0906
PP3_6: POGO_C3_CH1_VP; PogoPin_MillMax_0906
PP3_7: POGO_C3_CH1_VN; PogoPin_MillMax_0906
PP3_8: POGO_C3_CH2_IP; PogoPin_MillMax_0906
PP3_9: POGO_C3_CH2_IN; PogoPin_MillMax_0906
PP3_10: POGO_C3_CH2_VP; PogoPin_MillMax_0906
PP3_11: POGO_C3_CH2_VN; PogoPin_MillMax_0906
PP3_12: POGO_C3_CH3_IP; PogoPin_MillMax_0906
PP3_13: POGO_C3_CH3_IN; PogoPin_MillMax_0906
PP3_14: POGO_C3_CH3_VP; PogoPin_MillMax_0906
PP3_15: POGO_C3_CH3_VN; PogoPin_MillMax_0906
PP3_16: POGO_C3_RTD_FP; PogoPin_MillMax_0906
PP3_17: POGO_C3_RTD_FN; PogoPin_MillMax_0906
PP3_18: POGO_C3_RTD_SP; PogoPin_MillMax_0906
PP3_19: POGO_C3_RTD_SN; PogoPin_MillMax_0906
PP4_0: POGO_C4_CH0_IP; PogoPin_MillMax_0906
PP4_1: POGO_C4_CH0_IN; PogoPin_MillMax_0906
PP4_2: POGO_C4_CH0_VP; PogoPin_MillMax_0906
PP4_3: POGO_C4_CH0_VN; PogoPin_MillMax_0906
PP4_4: POGO_C4_CH1_IP; PogoPin_MillMax_0906
PP4_5: POGO_C4_CH1_IN; PogoPin_MillMax_0906
PP4_6: POGO_C4_CH1_VP; PogoPin_MillMax_0906
PP4_7: POGO_C4_CH1_VN; PogoPin_MillMax_0906
PP4_8: POGO_C4_CH2_IP; PogoPin_MillMax_0906
PP4_9: POGO_C4_CH2_IN; PogoPin_MillMax_0906
PP4_10: POGO_C4_CH2_VP; PogoPin_MillMax_0906
PP4_11: POGO_C4_CH2_VN; PogoPin_MillMax_0906
PP4_12: POGO_C4_CH3_IP; PogoPin_MillMax_0906
PP4_13: POGO_C4_CH3_IN; PogoPin_MillMax_0906
PP4_14: POGO_C4_CH3_VP; PogoPin_MillMax_0906
PP4_15: POGO_C4_CH3_VN; PogoPin_MillMax_0906
PP4_16: POGO_C4_RTD_FP; PogoPin_MillMax_0906
PP4_17: POGO_C4_RTD_FN; PogoPin_MillMax_0906
PP4_18: POGO_C4_RTD_SP; PogoPin_MillMax_0906
PP4_19: POGO_C4_RTD_SN; PogoPin_MillMax_0906
PP5_0: POGO_C5_CH0_IP; PogoPin_MillMax_0906
PP5_1: POGO_C5_CH0_IN; PogoPin_MillMax_0906
PP5_2: POGO_C5_CH0_VP; PogoPin_MillMax_0906
PP5_3: POGO_C5_CH0_VN; PogoPin_MillMax_0906
PP5_4: POGO_C5_CH1_IP; PogoPin_MillMax_0906
PP5_5: POGO_C5_CH1_IN; PogoPin_MillMax_0906
PP5_6: POGO_C5_CH1_VP; PogoPin_MillMax_0906
PP5_7: POGO_C5_CH1_VN; PogoPin_MillMax_0906
PP5_8: POGO_C5_CH2_IP; PogoPin_MillMax_0906
PP5_9: POGO_C5_CH2_IN; PogoPin_MillMax_0906
PP5_10: POGO_C5_CH2_VP; PogoPin_MillMax_0906
PP5_11: POGO_C5_CH2_VN; PogoPin_MillMax_0906
PP5_12: POGO_C5_CH3_IP; PogoPin_MillMax_0906
PP5_13: POGO_C5_CH3_IN; PogoPin_MillMax_0906
PP5_14: POGO_C5_CH3_VP; PogoPin_MillMax_0906
PP5_15: POGO_C5_CH3_VN; PogoPin_MillMax_0906
PP5_16: POGO_C5_RTD_FP; PogoPin_MillMax_0906
PP5_17: POGO_C5_RTD_FN; PogoPin_MillMax_0906
PP5_18: POGO_C5_RTD_SP; PogoPin_MillMax_0906
PP5_19: POGO_C5_RTD_SN; PogoPin_MillMax_0906
R1: 4.3K_0.1%_25ppm; R_0603
R2, R3: 10K; R_0603
U1: AD5940BCBZ-RL7; LFCSP-32_5x5mm_P0.5mm
U2, U3: ADG731BSUZ; TQFP-48_7x7mm_P0.5mm
U4: MAX31865ATP+; TQFN-20_5x5mm_P0.65mm

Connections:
+3V3: FB1.1, FB2.1, J1.1, R2.1, R3.1, U2.6, U3.6
AFE_AVDD: C1.1, C2.1, C4.1, C6.1, C7.1, C8.1, C9.1, C10.1, FB1.2, U1.1, U1.2, U2.5, U3.5, U4.17
AFE_DVDD: C3.1, C11.1, FB2.2, U1.21, U4.19
AFE_VBIAS_CAP: C5.1, U1.19
C1_CH0_IN: PP1_1.1, U2.8
C1_CH0_IP: PP1_0.1, U2.7
C1_CH0_VN: PP1_3.1, U2.10
C1_CH0_VP: PP1_2.1, U2.9
C1_CH1_IN: PP1_5.1, U2.12
C1_CH1_IP: PP1_4.1, U2.11
C1_CH1_VN: PP1_7.1, U2.15
C1_CH1_VP: PP1_6.1, U2.14
C1_CH2_IN: PP1_9.1, U2.17
C1_CH2_IP: PP1_8.1, U2.16
C1_CH2_VN: PP1_11.1, U2.20
C1_CH2_VP: PP1_10.1, U2.19
C1_CH3_IN: PP1_13.1, U2.22
C1_CH3_IP: PP1_12.1, U2.21
C1_CH3_VN: PP1_15.1, U2.24
C1_CH3_VP: PP1_14.1, U2.23
C1_RTD_FN: PP1_17.1, U2.28
C1_RTD_FP: PP1_16.1, U2.27
C1_RTD_SN: PP1_19.1, U2.30
C1_RTD_SP: PP1_18.1, U2.29
C2_CH0_IN: PP2_1.1, U2.32
C2_CH0_IP: PP2_0.1, U2.31
C2_CH0_VN: PP2_3.1, U2.34
C2_CH0_VP: PP2_2.1, U2.33
C2_CH1_IN: PP2_5.1, U2.36
C2_CH1_IP: PP2_4.1, U2.35
C2_CH1_VN: PP2_7.1, U2.39
C2_CH1_VP: PP2_6.1, U2.37
C2_CH2_IN: PP2_9.1, U2.41
C2_CH2_IP: PP2_8.1, U2.40
C2_CH2_VN: PP2_11.1, U2.43
C2_CH2_VP: PP2_10.1, U2.42
C3_CH0_IN: PP3_1.1, U3.8
C3_CH0_IP: PP3_0.1, U3.7
C3_CH0_VN: PP3_3.1, U3.10
C3_CH0_VP: PP3_2.1, U3.9
C3_CH1_IN: PP3_5.1, U3.12
C3_CH1_IP: PP3_4.1, U3.11
C3_CH1_VN: PP3_7.1, U3.15
C3_CH1_VP: PP3_6.1, U3.14
C3_CH2_IN: PP3_9.1, U3.17
C3_CH2_IP: PP3_8.1, U3.16
C3_CH2_VN: PP3_11.1, U3.20
C3_CH2_VP: PP3_10.1, U3.19
C3_CH3_IN: PP3_13.1, U3.22
C3_CH3_IP: PP3_12.1, U3.21
C3_CH3_VN: PP3_15.1, U3.24
C3_CH3_VP: PP3_14.1, U3.23
C3_RTD_FN: PP3_17.1, U3.28
C3_RTD_FP: PP3_16.1, U3.27
C3_RTD_SN: PP3_19.1, U3.30
C3_RTD_SP: PP3_18.1, U3.29
C4_CH0_IN: PP4_1.1, U3.32
C4_CH0_IP: PP4_0.1, U3.31
C4_CH0_VN: PP4_3.1, U3.34
C4_CH0_VP: PP4_2.1, U3.33
C4_CH1_IN: PP4_5.1, U3.36
C4_CH1_IP: PP4_4.1, U3.35
C4_CH1_VN: PP4_7.1, U3.39
C4_CH1_VP: PP4_6.1, U3.37
C4_CH2_IN: PP4_9.1, U3.41
C4_CH2_IP: PP4_8.1, U3.40
C4_CH2_VN: PP4_11.1, U3.43
C4_CH2_VP: PP4_10.1, U3.42
CS_AD5940: J1.6, U1.25
CS_ADG731_I: J1.8, U2.2
CS_ADG731_V: J1.9, U3.2
CS_MAX31865: J1.7, U4.3
DRDY_MAX31865: R2.2, U4.5
GND: C1.2, C2.2, C3.2, C4.2, C5.2, C6.2, C7.2, C8.2, C9.2, C10.2, C11.2, H1.1, H2.1, H3.1, H4.1, J1.2, U1.3, U1.20, U1.33, U2.13, U2.18, U2.25, U2.26, U2.38, U3.13, U3.18, U3.25, U3.26, U3.38, U4.11, U4.12, U4.18, U4.21
INT_AD5940: J1.10, R3.2, U1.30
MUX_I_OUT: U1.4, U1.9, U2.1
MUX_V_OUT: U1.5, U1.8, U3.1
RTD_FORCE_N: U4.6, U4.14
RTD_FORCE_P: R1.2, U4.15, U4.16, U4.20
RTD_REF_N: C12.2, U4.7
RTD_REF_P: C12.1, R1.1, U4.8
RTD_SENSE_N: C13.2, U4.9
RTD_SENSE_P: C13.1, U4.10
SPI_MISO: J1.5, U1.27, U4.1
SPI_MOSI: J1.4, U1.28, U2.3, U3.3, U4.2
SPI_SCLK: J1.3, U1.26, U2.4, U3.4, U4.4

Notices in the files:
pcb/lamp_rev_a/lamp_rev_a.kicad_pcb:
CERN-OHL-S v2
